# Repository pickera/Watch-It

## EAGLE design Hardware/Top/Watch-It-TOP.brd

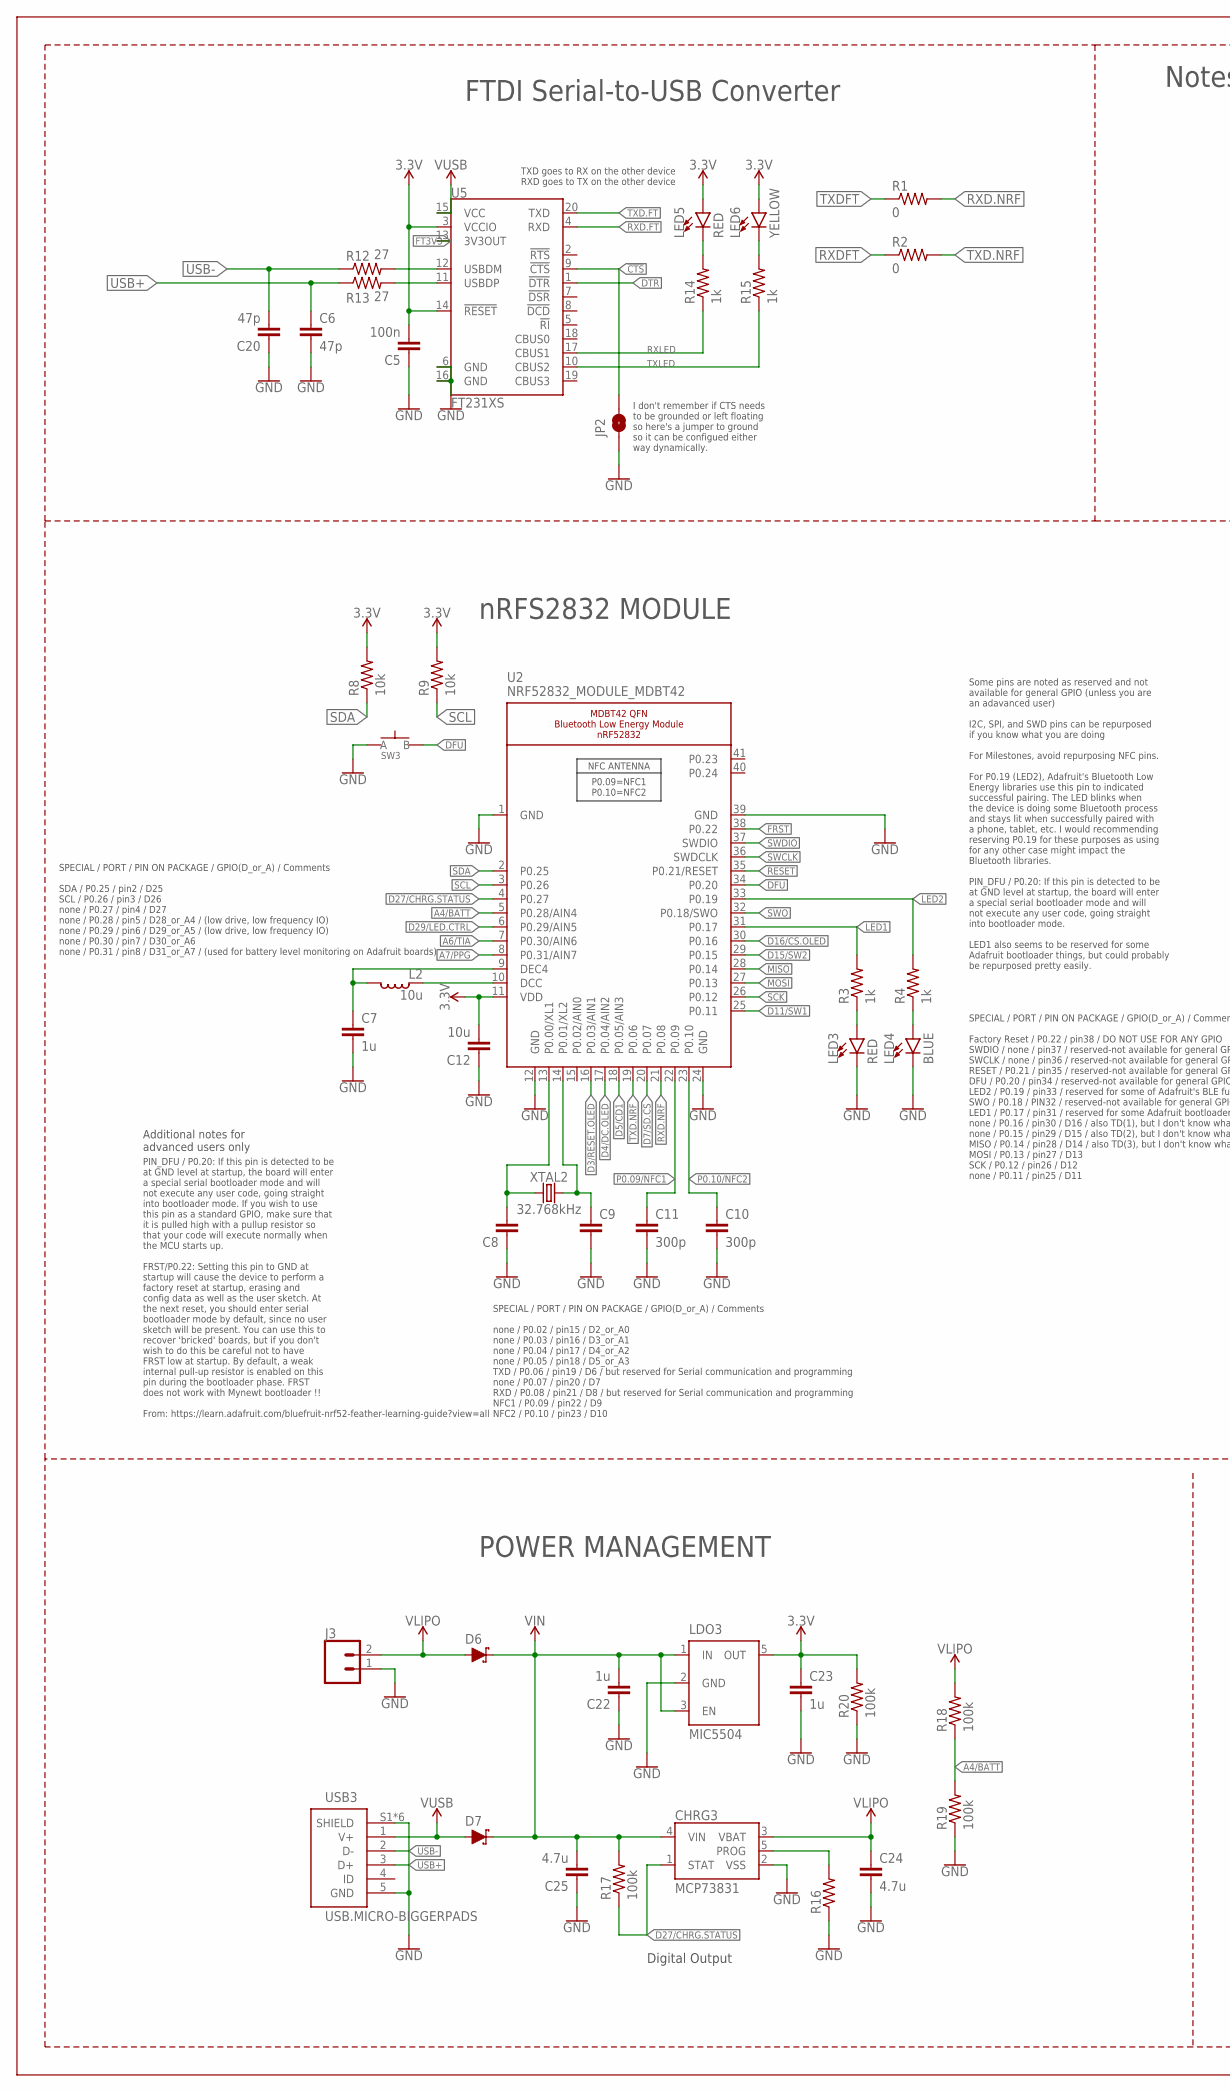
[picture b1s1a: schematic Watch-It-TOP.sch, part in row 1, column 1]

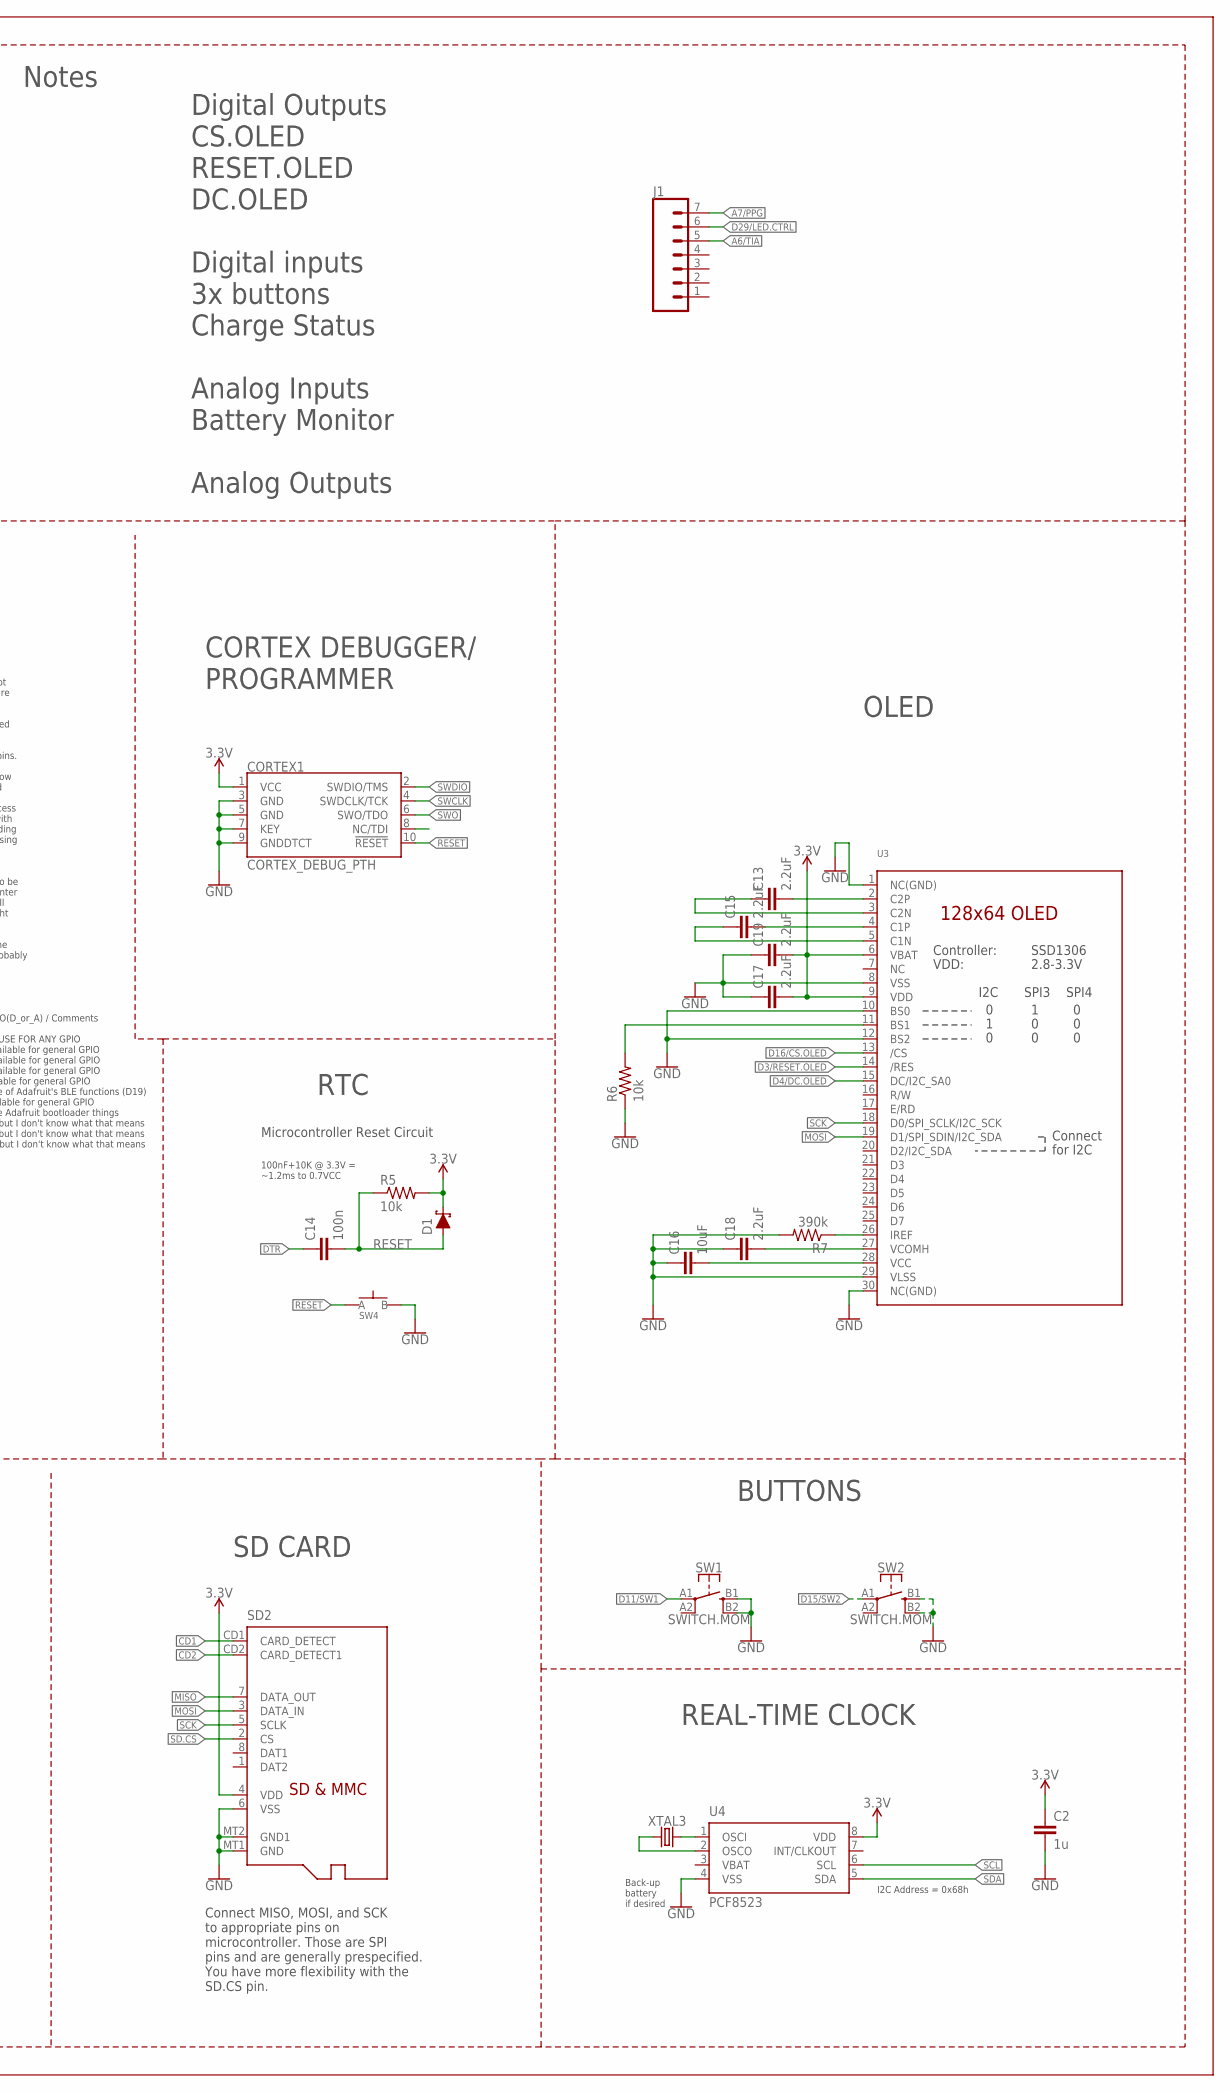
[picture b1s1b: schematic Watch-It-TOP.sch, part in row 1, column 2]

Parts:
C2, C7, C22, C23: 1u; C0603
C5, C14: 100n; C0603
C6, C20: 47p; C0603
C8, C9: CAPACITOR0603; C0603
C10, C11: 300p; C0603
C12: 10u; C0805
C13, C15, C17, C18, C19: 2.2uF; C0402
C16: 10uF; C0603
C24, C25: 4.7u; C0603
CHRG3: MCP73831; SOT23-5
CORTEX1: CORTEX_DEBUG_PTH; 2X5-PTH-1.27MM
D1, D6, D7: SCHOTTKY-USC; USC
J1: CONN_07; 1X07
J3: CONN_02; 1X02
JP2: JUMPER-SMT_2_NO_SILK; SMT-JUMPER_2_NO_SILK
L2: 10u; L0603
LDO3: MIC5504; SOT23-5
LED3, LED5: RED; LED-0603
LED4: BLUE; LED-0603
LED6: YELLOW; LED-0603
R1, R2: 0; R0603
R3, R4, R14, R15: 1k; R0603
R5, R6, R8, R9: 10k; R0603
R7: 390k; R0603
R12, R13: 27; R0603
R16: RESISTOR0603; R0603
R17, R18, R19, R20: 100k; R0603
SD2: MICROSD
SW1, SW2: SWITCH.MOM; TACTILE_SWITCH_SMD_6.2MM_TALL
SW3, SW4: SPST-PTS830GG140-COPY.1-3; BUTTON-GULLWING
U2: NRF52832_MODULE_MDBT42; BLE_MODULE_RAYTAC_MDBT42
U3: DISP_OLED_UG-2864HSWEG01-NO-WRAPAROUND; UG-2864HSWEG01_0.96IN_NO-WRAPAROUND
U4: PCF8523; SO8; DIGIKEY 568-5306-1-ND
U5: FT231XS; SSOP20_L
USB3: USB.MICRO-BIGGERPADS; USB-MICRO-01.BIGGERPADS
XTAL2: 32.768kHz; 2-SMD.NOLEAD.2.0MMTO1.2MM
XTAL3: 32.7680kHz; 2-SMD.NOLEAD.2.0MMTO1.2MM

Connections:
3.3V: C2.1, C5.2, C12.2, C17.2, C19.2, C23.1, CORTEX1.1 (VCC), D1.- (C), LDO3.5 (OUT), LED5.A, LED6.A, R5.2, R8.2, R9.2, R20.2, SD2.4 (VDD), U2.11 (VDD), U3.6 (VBAT), U3.9 (VDD), U4.8 (VDD), U5.3 (VCCIO), U5.14 (!RESET)
!CTS: JP2.2, U5.9 (!CTS)
A4/BATT: R18.1, R19.2, U2.5 (P0.28/AIN4)
A6/TIA: J1.5, U2.7 (P0.30/AIN6)
A7/PPG: J1.7, U2.8 (P0.31/AIN7)
CD1: SD2.CD1 (CARD_DETECT)
CD2: SD2.CD2 (CARD_DETECT1)
D3/RESET.OLED: U2.16 (P0.03/AIN1), U3.14 (/RES)
D4/DC.OLED: U2.17 (P0.04/AIN2), U3.15 (DC/I2C_SA0)
D5/CD1: U2.18 (P0.05/AIN3)
D7/SD.CS: U2.20 (P0.07)
D11/SW1: SW1.A1 (1), U2.25 (P0.11)
D15/SW2: SW2.A1 (1), U2.29 (P0.15)
D16/CS.OLED: U2.30 (P0.16), U3.13 (/CS)
D27/CHRG.STATUS: CHRG3.1 (STAT), R17.1, U2.4 (P0.27)
D29/LED.CTRL: J1.6, U2.6 (P0.29/AIN5)
DFU: SW3.3 (B), U2.34 (P0.20)
DTR: C14.1, U5.1 (!DTR)
FRST: U2.38 (P0.22)
FT3V3: U5.13 (3V3OUT)
GND: C2.2, C5.1, C6.2, C7.2, C8.1, C9.2, C10.2, C11.2, C12.1, C16.1, C17.1, C18.1, C19.1, C20.1, C22.1, C23.2, C24.2, C25.1, CHRG3.2 (VSS), CORTEX1.3 (GND), CORTEX1.5 (GND), CORTEX1.7 (KEY), CORTEX1.9 (GNDDTCT), J3.1, JP2.1, LDO3.2 (GND), LED3.C, LED4.C, R6.1, R7.2, R16.1, R19.1, R20.1, SD2.6 (VSS), SD2.MT1 (GND), SD2.MT2 (GND1), SW1.B1 (3), SW1.B2 (4), SW2.B1 (3), SW2.B2 (4), SW3.1 (A), SW4.3 (B), U2.1 (GND), U2.12 (GND), U2.24 (GND), U2.39 (GND), U3.1 (NC(GND)), U3.8 (VSS), U3.10 (BS0), U3.12 (BS2), U3.29 (VLSS), U3.30 (NC(GND)), U4.4 (VSS), U5.6 (GND), U5.16 (GND), USB3.5 (GND), USB3.S1 (SHIELD), USB3.S2 (SHIELD), USB3.S3 (SHIELD), USB3.S4 (SHIELD), USB3.S5 (SHIELD), USB3.S6 (SHIELD)
LED1: R3.2, U2.31 (P0.17)
LED2: R4.2, U2.33 (P0.19)
MISO: SD2.7 (DATA_OUT), U2.28 (P0.14)
MOSI: SD2.3 (DATA_IN), U2.27 (P0.13), U3.19 (D1/SPI_SDIN/I2C_SDA)
unnamed: R6.2, U3.11 (BS1)
unnamed: R7.1, U3.26 (IREF)
unnamed: C13.2, U3.2 (C2P)
unnamed: C8.2, U2.13 (P0.00/XL1), XTAL2.P$1 (1)
unnamed: C13.1, U3.3 (C2N)
unnamed: C9.1, U2.14 (P0.01/XL2), XTAL2.P$2 (2)
unnamed: C15.2, U3.4 (C1P)
unnamed: C15.1, U3.5 (C1N)
unnamed: LED3.A, R3.1
unnamed: LED4.A, R4.1
unnamed: L2.1, U2.10 (DCC)
unnamed: C7.1, L2.2, U2.9 (DEC4)
unnamed: C16.2, U3.28 (VCC)
unnamed: C18.2, U3.27 (VCOMH)
unnamed: CHRG3.5 (PROG), R16.2
unnamed: U4.2 (OSCO), XTAL3.P$1 (1)
unnamed: U4.1 (OSCI), XTAL3.P$2 (2)
unnamed: R12.2, U5.12 (USBDM)
unnamed: R13.2, U5.11 (USBDP)
unnamed: LED5.C, R14.2
unnamed: LED6.C, R15.2
P0.09/NFC1: C11.1, U2.22 (P0.09)
P0.10/NFC2: C10.1, U2.23 (P0.10)
RESET: C14.2, CORTEX1.10 (!RESET), D1.+ (A), R5.1, SW4.1 (A), U2.35 (P0.21/RESET)
RXD.FT: U5.4 (RXD)
RXD.NRF: R1.2, U2.21 (P0.08)
RXDFT: R2.1
RXLED: R14.1, U5.17 (CBUS1)
SCK: SD2.5 (SCLK), U2.26 (P0.12), U3.18 (D0/SPI_SCLK/I2C_SCK)
SCL: R9.1, U2.3 (P0.26), U4.6 (SCL)
SD.CS: SD2.2 (CS)
SDA: R8.1, U2.2 (P0.25), U4.5 (SDA)
SWCLK: CORTEX1.4 (SWDCLK/TCK), U2.36 (SWDCLK)
SWDIO: CORTEX1.2 (SWDIO/TMS), U2.37 (SWDIO)
SWO: CORTEX1.6 (SWO/TDO), U2.32 (P0.18/SWO)
TXD.FT: U5.20 (TXD)
TXD.NRF: R2.2, U2.19 (P0.06)
TXDFT: R1.1
TXLED: R15.1, U5.10 (CBUS2)
USB+: C6.1, R13.1, USB3.3 (D+)
USB-: C20.2, R12.1, USB3.2 (D-)
VBAT: U4.3 (VBAT)
VIN: C22.2, C25.2, CHRG3.4 (VIN), D6.- (C), D7.- (C), LDO3.1 (IN), LDO3.3 (EN), R17.2
VLIPO: C24.1, CHRG3.3 (VBAT), D6.+ (A), J3.2, R18.2
V_USB: D7.+ (A), U5.15 (VCC), USB3.1 (V+)

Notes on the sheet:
Microcontroller Reset Circuit
100nF+10K @ 3.3V = ~1.2ms to 0.7VCC
SPECIAL / PORT / PIN ON PACKAGE / GPIO(D_or_A) / Comments SDA / P0.25 / pin2 / D25 SCL / P0.26 / pin3 / D26 none / P0.27 / pin4 / D27 none / P0.28 / pin5 / D28_or_A4 / (low drive, low frequency IO) none / P0.29 / pin6 / D29_or_A5 / (low drive, low frequency IO) none / P0.30 / pin7 / D30_or_A6 none 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
SPECIAL / PORT / PIN ON PACKAGE / GPIO(D_or_A) / Comments none / P0.02 / pin15 / D2_or_A0 none / P0.03 / pin16 / D3_or_A1 none / P0.04 / pin17 / D4_or_A2 none / P0.05 / pin18 / D5_or_A3 TXD / P0.06 / pin19 / D6 / but reserved for Serial communication and programming none / P0.07 / pin20 / D7 RXD / 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
SPECIAL / PORT / PIN ON PACKAGE / GPIO(D_or_A) / Comments Factory Reset / P0.22 / pin38 / DO NOT USE FOR ANY GPIO SWDIO / none / pin37 / reserved-not available for general GPIO SWCLK / none / pin36 / reserved-not available for general GPIO RESET / P0.21 / pin35 / reserved-not available for general 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
Some pins are noted as reserved and not available for general GPIO (unless you are an adavanced user) I2C, SPI, and SWD pins can be repurposed if you know what you are doing For Milestones, avoid repurposing NFC pins. For P0.19 (LED2), Adafruit's Bluetooth Low Energy libraries use this pin to indic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
PIN_DFU / P0.20: If this pin is detected to be at GND level at startup, the board will enter a special serial bootloader mode and will not execute any user code, going straight into bootloader mode. If you wish to use this pin as a standard GPIO, make sure that it is pulled high with a pullup resis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
Additional notes for advanced users only
Connect MISO, MOSI, and SCK to appropriate pins on microcontroller. Those are SPI pins and are generally prespecified. You have more flexibility with the SD.CS pin.
I2C Address = 0x68h
Back-up battery if desired
RTC
OLED
BUTTONS
REAL-TIME CLOCK
SD CARD
POWER MANAGEMENT
CORTEX DEBUGGER/ PROGRAMMER
nRFS2832 MODULE
Digital Outputs CS.OLED RESET.OLED DC.OLED Digital inputs 3x buttons Charge Status Analog Inputs Battery Monitor Analog Outputs
TXD goes to RX on the other device RXD goes to TX on the other device
I don't remember if CTS needs to be grounded or left floating so here's a jumper to ground so it can be configued either way dynamically.
FTDI Serial-to-USB Converter
Notes
Digital Output

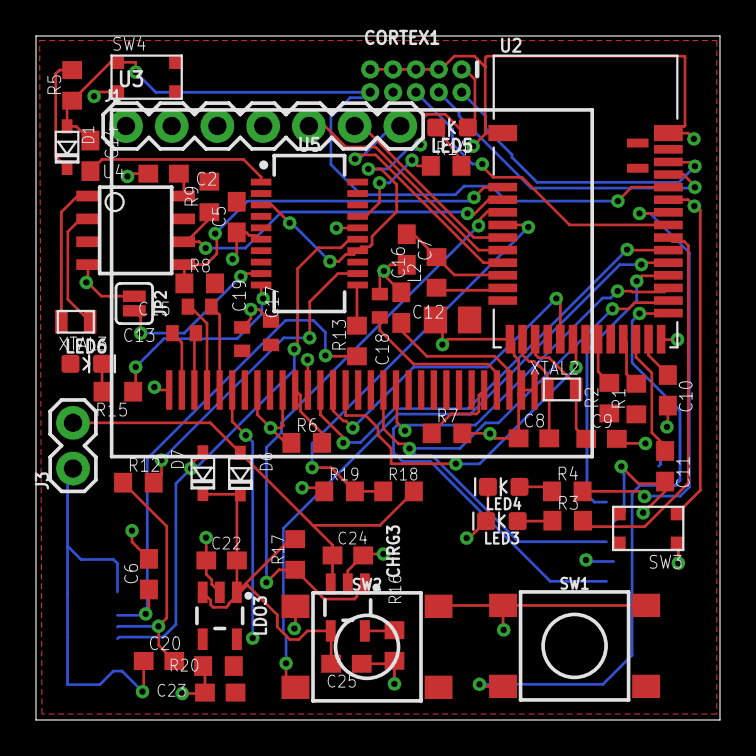
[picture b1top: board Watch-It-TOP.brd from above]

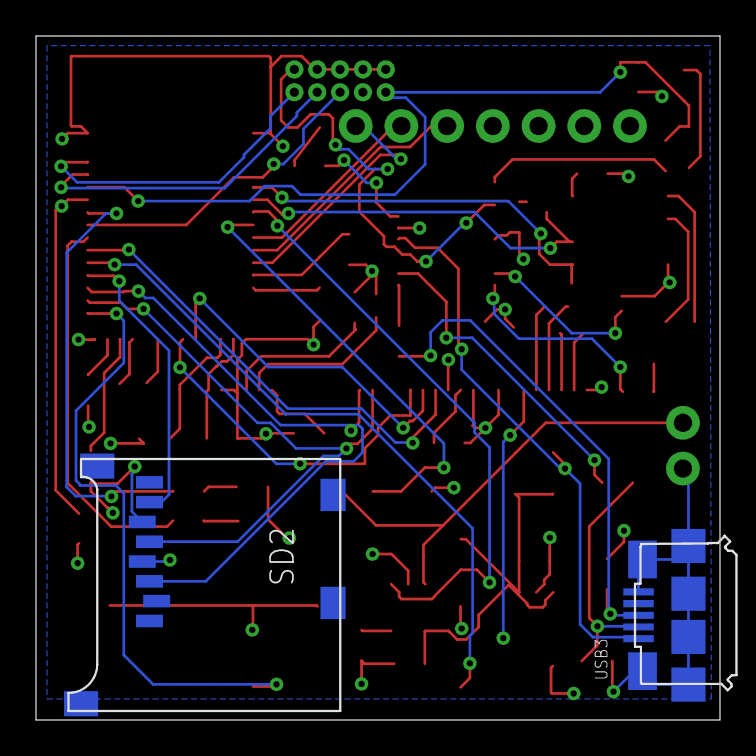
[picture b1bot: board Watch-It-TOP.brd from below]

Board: 2 copper layers, 38.0 x 38.0 mm, 65 parts (2 on the bottom side), 58 nets.

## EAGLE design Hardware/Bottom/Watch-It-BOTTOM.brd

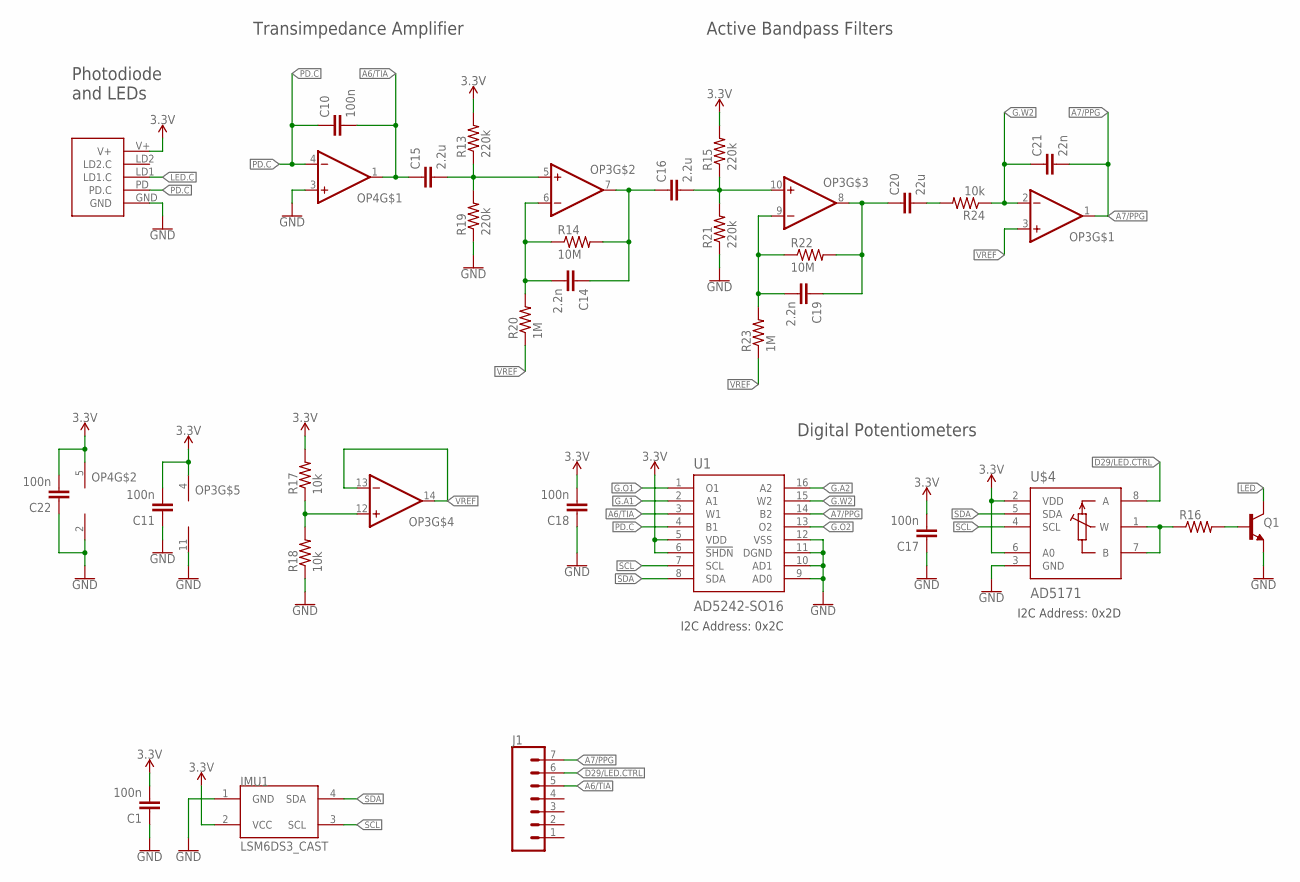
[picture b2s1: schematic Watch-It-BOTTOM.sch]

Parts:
C1, C10, C11, C17, C18, C22: 100n; C0603
C14, C19: 2.2n; C0603
C15, C16: 2.2u; C0603
C20: 22u; C0603
C21: 22n; C0603
IMU1: LSM6DS3_CAST
J1: CONN_07; 1X07
OP3: OP-QUAD-SO14; SO14
OP4: OP-SINGLEOT; SOT23-5
Q1: NPN-GENERIC; SOT23-3
R13, R15, R19, R21: 220k; R0603
R14, R22: 10M; R0603
R16: RESISTOR0603; R0603
R17, R18: 10k; R0402
R20, R23: 1M; R0603
R24: 10k; R0603
U1: AD5242-SO16; SO16
U$3: PPG.MODULE.2
U$4: AD5171; SOT-23-8

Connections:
3.3V: C1.2, C11.2, C17.2, C18.2, C22.2, IMU1.2 (VCC), OP3.4 (V+), OP4.5 (V+), R13.2, R15.2, R17.2, U1.5 (VDD), U1.6 (!SHDN), U$3.V+, U$4.2 (VDD), U$4.6 (A0)
A6/TIA: C10.2, C15.1, J1.5, OP4.1 (OUT), U1.3 (W1)
A7/PPG: C21.2, J1.7, OP3.1 (OUT), U1.14 (B2)
D29/LED.CTRL: J1.6, U$4.8 (A)
G.A1: U1.2 (A1)
G.A2: U1.16 (A2)
G.O1: U1.1 (O1)
G.O2: U1.13 (O2)
G.W2: C21.1, OP3.2 (-IN), R24.1, U1.15 (W2)
GND: C1.1, C11.1, C17.1, C18.1, C22.1, IMU1.1 (GND), OP3.11 (V-), OP4.2 (V-), OP4.3 (+IN), Q1.2 (E), R18.1, R19.1, R21.1, U1.9 (AD0), U1.10 (AD1), U1.11 (DGND), U1.12 (VSS), U$3.GND, U$4.3 (GND)
LED: Q1.3 (C)
LED.C: U$3.LD1 (LD1.C)
unnamed: Q1.1 (B), R16.2
unnamed: R16.1, U$4.1 (W), U$4.7 (B)
unnamed: OP3.12 (+IN), R17.1, R18.2
unnamed: C15.2, OP3.5 (+IN), R13.1, R19.2
unnamed: C14.2, OP3.6 (-IN), R14.1, R20.2
unnamed: C14.1, C16.1, OP3.7 (OUT), R14.2
unnamed: C16.2, OP3.10 (+IN), R15.1, R21.2
unnamed: C19.2, OP3.9 (-IN), R22.1, R23.2
unnamed: C19.1, C20.1, OP3.8 (OUT), R22.2
unnamed: C20.2, R24.2
PD.C: C10.1, OP4.4 (-IN), U1.4 (B1), U$3.PD (PD.C)
SCL: IMU1.3 (SCL), U1.7 (SCL), U$4.4 (SCL)
SDA: IMU1.4 (SDA), U1.8 (SDA), U$4.5 (SDA)
VREF: OP3.3 (+IN), OP3.13 (-IN), OP3.14 (OUT), R20.1, R23.1

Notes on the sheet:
Photodiode and LEDs
Active Bandpass Filters
Digital Potentiometers
Transimpedance Amplifier
I2C Address: 0x2C
I2C Address: 0x2D

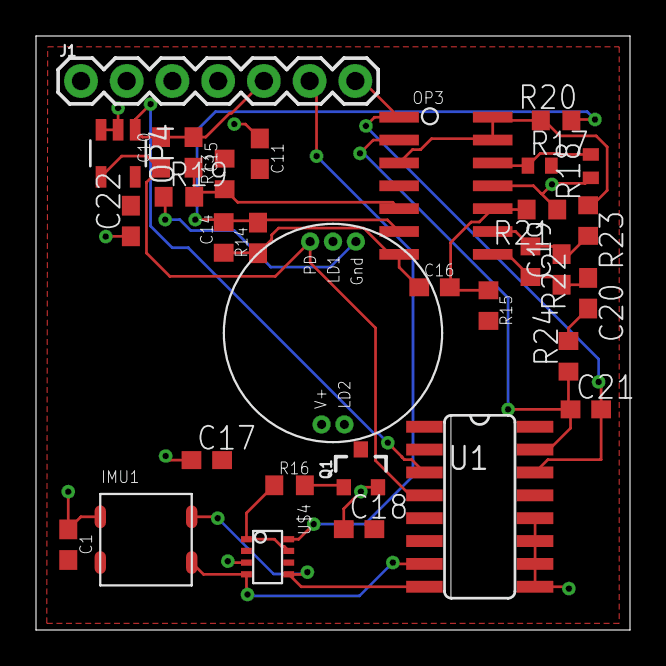
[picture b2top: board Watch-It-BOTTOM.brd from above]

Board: 2 copper layers, 33.0 x 33.0 mm, 32 parts (0 on the bottom side), 20 nets.

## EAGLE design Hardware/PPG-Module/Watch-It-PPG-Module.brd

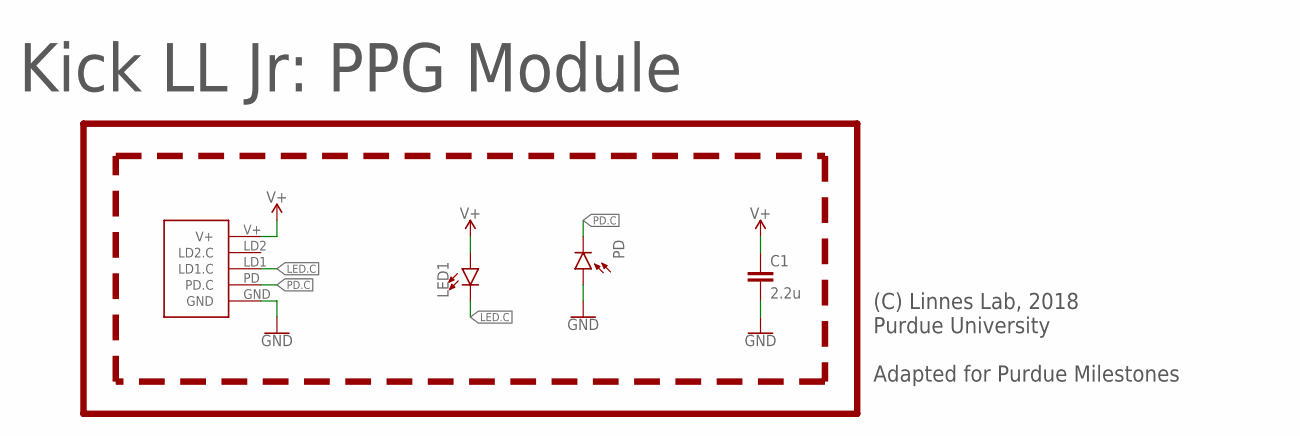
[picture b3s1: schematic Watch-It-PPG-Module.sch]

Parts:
C1: 2.2u; C0603
J1: PPG.MODULE.2
LED1: LED0805; LED-0805
PD: PHOTODIODE.-SMD.GULLWING; 2-SMD.GULLWING
U$3: LINNES.LAB.LOGO

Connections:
GND: C1.2, J1.GND, PD.+ (A)
LED.C: J1.LD1 (LD1.C), LED1.C
PD.C: J1.PD (PD.C), PD.- (C)
V+: C1.1, J1.V+, LED1.A

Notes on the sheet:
Kick LL Jr: PPG Module
(C) Linnes Lab, 2018 Purdue University Adapted for Purdue Milestones

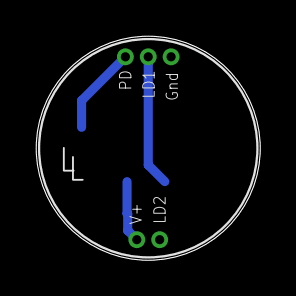
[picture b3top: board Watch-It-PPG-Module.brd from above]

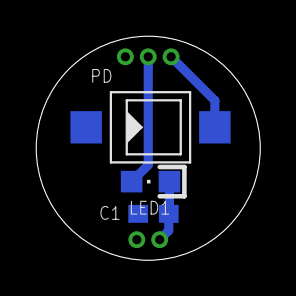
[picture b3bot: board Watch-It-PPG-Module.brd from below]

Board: 2 copper layers, 12.4 x 12.4 mm, 5 parts (3 on the bottom side), 4 nets.

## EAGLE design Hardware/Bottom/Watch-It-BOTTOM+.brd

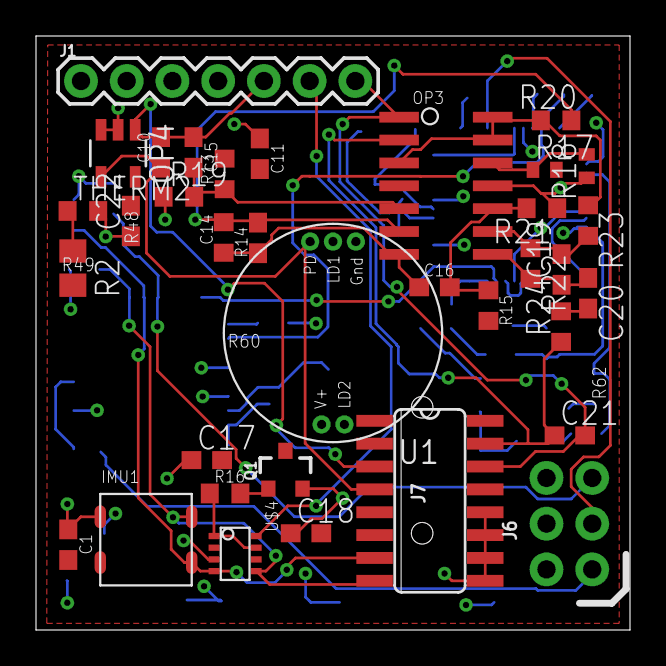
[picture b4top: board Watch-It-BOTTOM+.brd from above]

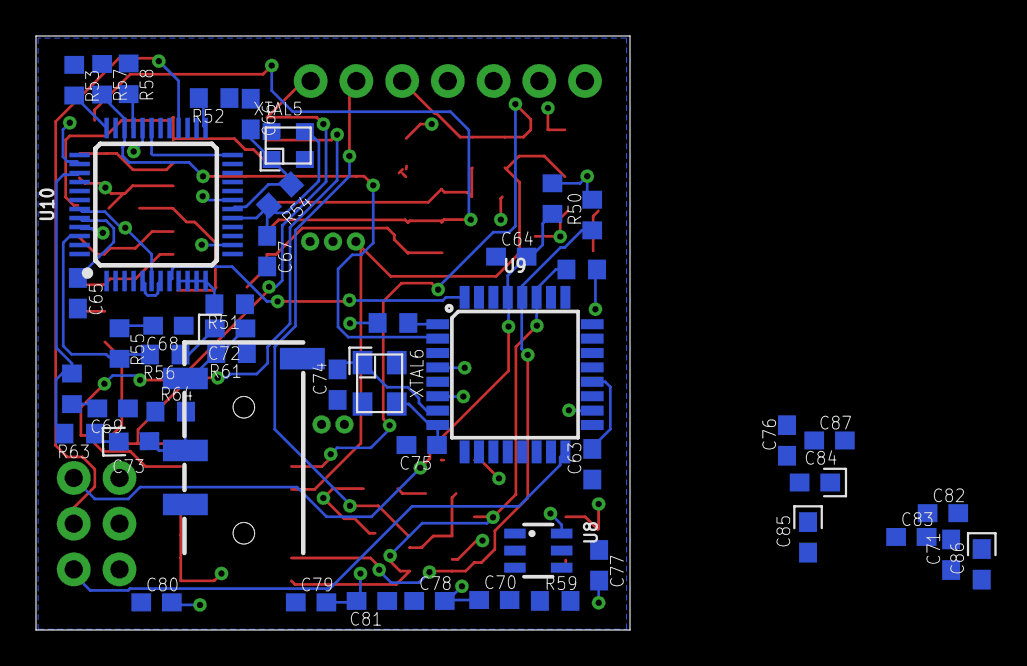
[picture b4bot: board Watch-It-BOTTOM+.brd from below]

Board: 2 copper layers, 33.0 x 33.0 mm, 83 parts (48 on the bottom side), 50 nets.

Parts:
C1, C10, C11, C17, C18, C22, C63, C64, C76, C78, C79, C80, C81, C82, C87: 100n; C0603
C14, C19: 2.2n; C0603
C15, C16: 2.2u; C0603
C20: 22u; C0603
C21: 22n; C0603
C65, C70, C71, C77, C83: 1u; C0603
C66, C67, C74, C75: 33p; C0603
C68, C69: 10n; C0603
C72, C73, C84, C85, C86: 10u; C0603.POLAR
IMU1: LSM6DS3_CAST
J1: 1X07
J6: AVR_SPI_PROG_3X2NS; 2X3-NS
J7: AUDIO_JACK_3.5MM_TRRS_SMD_RA
OP3: SO14
OP4: SOT23-5
Q1: SOT23-3
R2: 10k; R0805
R13, R15, R19, R21: 220k; R0603
R14, R22: 10M; R0603
R16: R0603
R17, R18: 10k; R0402
R20, R23, R54: 1M; R0603
R24, R48, R49, R50, R61, R64: 10k; R0603
R51, R52, R53, R57, R58, R59, R60: 100k; R0603
R55, R62: 20; R0603
R56, R63: 470; R0603
THERM2: 10k; R0603
U1: AD5242-SO16; SO16
U8: SOT23-6
U9: ATMEGA328P_TQFP; TQFP32-08
U10: VS1053B; LQFP-48
U$3: PPG.MODULE.2
U$4: AD5171; SOT-23-8
XTAL5: 12.288MHz; 4-SMD.NOLEAD
XTAL6: 8MHz; 4-SMD.NOLEAD.3.25MM-2.5MM

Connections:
1.8V: C71.1, C82.2, C83.2, C86.A, U8.1, U10.5, U10.7, U10.24, U10.31
3.3V: C1.2, C11.2, C17.2, C18.2, C22.2, C70.1, C76.2, C77.2, C78.2, C79.2, C80.2, C81.2, C84.A, C85.A, C87.2, IMU1.2, J6.2, OP3.4, OP4.5, R2.2, R13.2, R15.2, R17.2, R48.2, R49.2, R50.2, R60.2, U1.5, U1.6, U8.6, U9.4, U9.6, U9.18, U10.6, U10.14, U10.19, U10.32, U10.38, U10.43, U10.45, U$3.V+, U$4.2, U$4.6
A6/TIA: C10.2, C15.1, J1.5, OP4.1, U1.3
A7/PPG: C21.2, J1.7, OP3.1, U1.14
D29/LED.CTRL: J1.6, U$4.8
G.W2: C21.1, OP3.2, R24.1, U1.15
GND: C1.1, C11.1, C17.1, C18.1, C22.1, C63.1, C65.2, C66.1, C67.2, C68.1, C69.1, C70.2, C71.2, C74.1, C75.2, C76.1, C77.1, C78.1, C79.1, C80.1, C81.1, C82.1, C83.1, C84.C, C85.C, C86.C, C87.1, IMU1.1, J6.6, J7.GND, J7.GND/MIC, OP3.11, OP4.2, OP4.3, Q1.2, R18.1, R19.1, R21.1, R51.1, R52.1, R53.1, R57.1, R58.1, R59.1, R61.1, R64.1, THERM2.2, U1.9, U1.10, U1.11, U1.12, U8.2, U9.3, U9.5, U9.21, U10.4, U10.16, U10.20, U10.21, U10.22, U10.35, U10.37, U10.40, U10.41, U10.47, U$3.GND, U$4.3
GPIO2: R58.2, U10.33
LEFT: R55.2, R56.2, U10.46
MIDI-RX: R60.1, U9.1, U10.26
MP3-CS: U9.10, U10.23
MP3-DCS: U9.11, U10.13
MP3-DREQ: U9.32, U10.8
MP3-GPIO1: R57.2, U9.2, U10.34
MP3-MISO: J6.1, U9.16, U10.30
MP3-MOSI: J6.4, U9.15, U10.29
MP3-RST-ATMEGA: C64.2, J6.5, R48.1, U9.29
MP3-RST-VS: U9.12, U10.3
MP3-SCK: J6.3, U9.17, U10.28
unnamed: Q1.1, R16.2
unnamed: R16.1, U$4.1, U$4.7
unnamed: OP3.12, R17.1, R18.2
unnamed: C15.2, OP3.5, R13.1, R19.2
unnamed: C14.2, OP3.6, R14.1, R20.2
unnamed: C14.1, C16.1, OP3.7, R14.2
unnamed: C16.2, OP3.10, R15.1, R21.2
unnamed: C19.2, OP3.9, R22.1, R23.2
unnamed: C19.1, C20.1, OP3.8, R22.2
unnamed: C20.2, R24.2
unnamed: C63.2, U9.20
unnamed: C66.2, R54.2, U10.18, XTAL5.XTAL1
unnamed: C67.1, R54.1, U10.17, XTAL5.XTAL2
unnamed: R51.2, U10.9, U10.10, U10.11, U10.12
unnamed: R52.2, U10.25
unnamed: R53.2, U10.36
unnamed: C65.1, U10.44
unnamed: C68.2, R55.1
unnamed: C72.A, R56.1
unnamed: C69.2, R62.1
unnamed: C73.A, R63.1
unnamed: C74.2, U9.7, XTAL6.XTAL1
unnamed: C75.1, U9.8, XTAL6.XTAL2
PD.C: C10.1, OP4.4, U1.4, U$3.PD
RIGHT: R62.2, R63.2, U10.39
SCL: IMU1.3, R50.1, U1.7, U9.28, U$4.4
SDA: IMU1.4, R49.1, U1.8, U9.27, U$4.5
SPK-L: C72.C, J7.LEFT, R61.2
SPK-R: C73.C, J7.RIGHT, R64.2
THERM: R2.1, THERM2.1
VREF: OP3.3, OP3.13, OP3.14, R20.1, R23.1

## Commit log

2020-05-28 device name and features
2020-06-01 smartwatch video 1
2020-06-04 organized repo
2020-06-04 did some routing
2020-06-10 routed bottom board 6/10
2020-06-11 routing
2020-06-11 rotated
2020-06-12 rotated and added pins
2020-06-12 made connections and added pins
2020-06-25 OOP video
2020-07-03 Almost done routing
2020-07-03 week 4 edits
2020-07-03 pushing old edits
2020-07-09 added PPG files
2020-07-09 finished routing
2020-07-09 fixed polygon and wire stubs
2020-07-16 added ambient light sensor
2020-07-16 added thermistor
2020-07-17 cleaned it up a bit
2020-07-30 more routing
